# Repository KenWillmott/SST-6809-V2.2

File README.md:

# SST-6809-V2.2
This is the working repository for the most current and only recommended version of the SST-6809.
It contains all of the files and reference documents, and some documentation. However, the full documentation set will be hosted elsewhere, location is yet to be determined. For now, you can follow the documentation in the old repo "SST-6809" which is mostly concordant with this new version.

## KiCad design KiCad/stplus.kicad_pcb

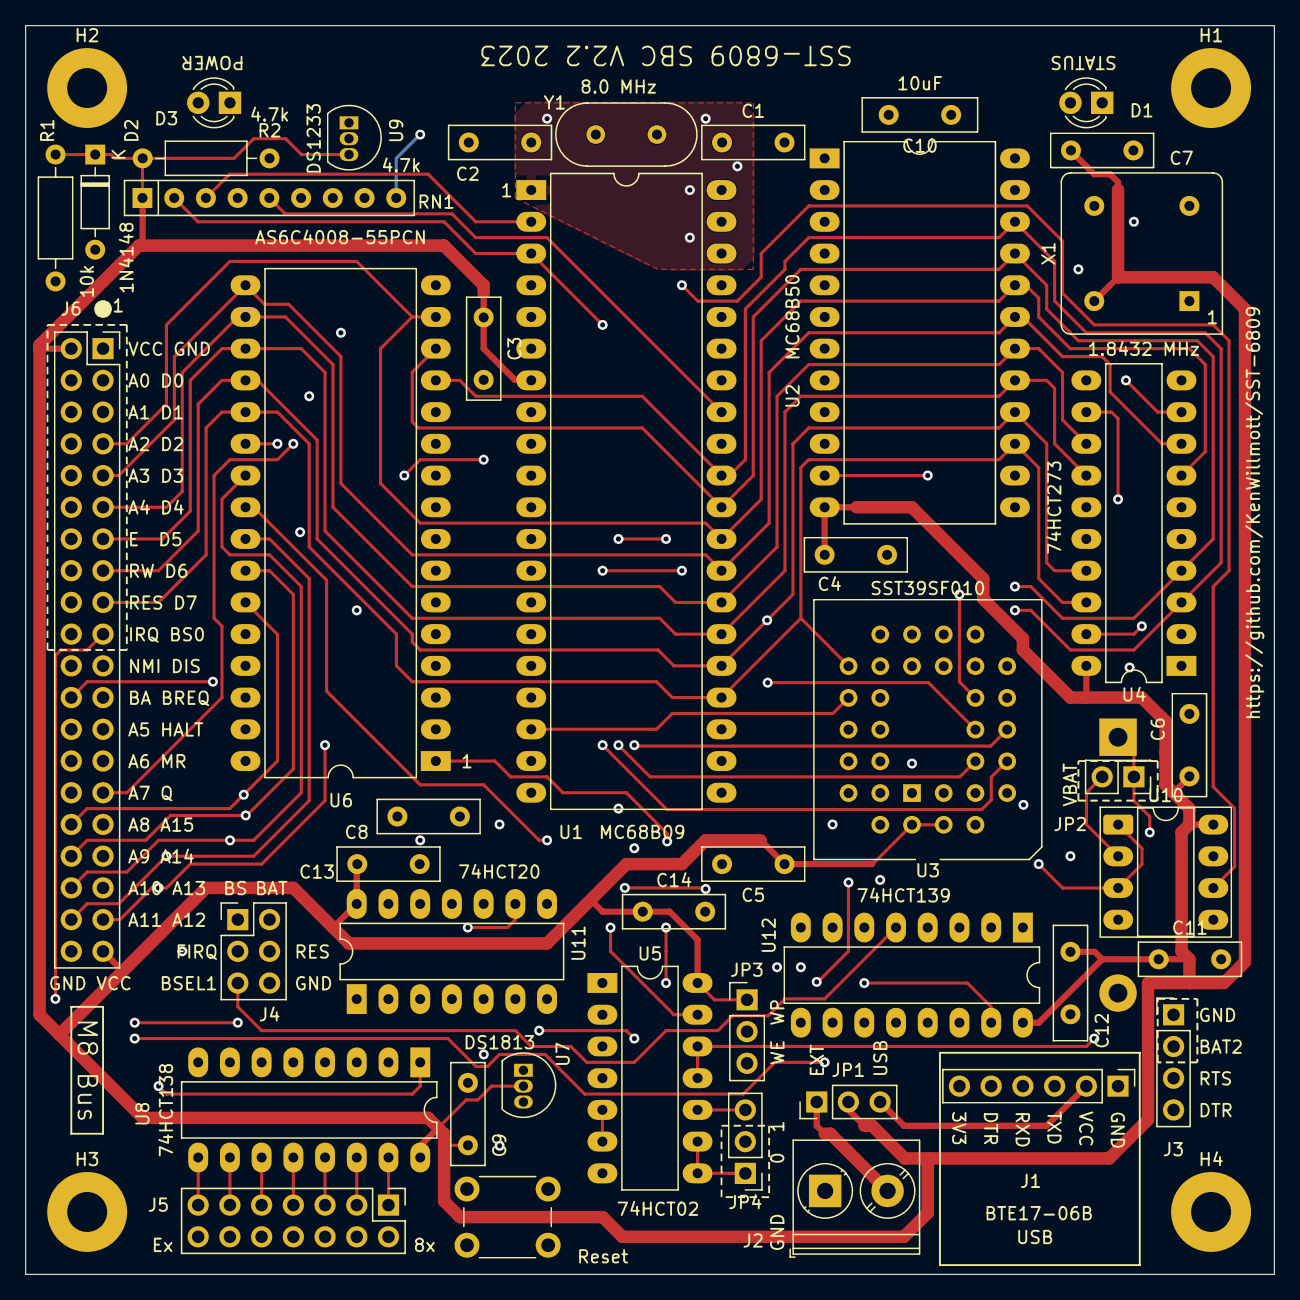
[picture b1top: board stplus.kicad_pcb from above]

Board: 4 copper layers, 100.0 x 100.0 mm, 50 parts (1 on the bottom side), 88 nets.

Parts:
BT1: 3.0V; BatteryHolder_Keystone_103_1x20mm
C1, C2: 20pF; C_Disc_D8.0mm_W2.5mm_P5.00mm
C3, C4, C5, C6, C7, C8, C9, C11, C13, C14: 100nF; C_Disc_D8.0mm_W2.5mm_P5.00mm
C10: 10uF; C_Disc_D9.0mm_W2.5mm_P5.00mm
C12: 100nF; C_Disc_D9.0mm_W2.5mm_P5.00mm
D1: STAT; LED_D3.0mm
D2: 1N4148; D_DO-35_SOD27_P7.62mm_Horizontal
D3: PWR; LED_D3.0mm
H1, H2, H3, H4: MountingHole_Pad; MountingHole_3.2mm_M3_Pad
J1: Conn_01x06_Pin; PinHeader_1x06_P2.54mm_Vertical
J2: Screw_Terminal_01x02; TerminalBlock_Phoenix_PT-1,5-2-5.0-H_1x02_P5.00mm_Horizontal
J3: Conn_01x04_Pin; PinHeader_1x04_P2.54mm_Vertical
J4: Conn_02x03_Odd_Even; PinHeader_2x03_P2.54mm_Vertical
J5: Conn_02x07_Odd_Even; PinHeader_2x07_P2.54mm_Vertical
J6: Conn_02x20_Odd_Even; PinSocket_2x20_P2.54mm_Vertical
JP1, JP3, JP4: Jumper_3_Bridged12; PinHeader_1x03_P2.54mm_Vertical
JP2: VBAT; PinHeader_2x01_P2.54mm_Vertical
R1: 10k; R_Axial_DIN0207_L6.3mm_D2.5mm_P10.16mm_Horizontal
R2: 4.7k; R_Axial_DIN0207_L6.3mm_D2.5mm_P10.16mm_Horizontal
RN1: 4.7k; R_Array_SIP9
SW1: Reset; SW_PUSH_6mm_H5mm
U1: MC68B09; DIP-40_W15.24mm_LongPads
U2: MC68B50; DIP-24_W15.24mm_LongPads
U3: SST39SF010; PLCC-32_THT-Socket
U4: 74HCT273; DIP-20_W7.62mm_LongPads
U5: 74HCT02; DIP-14_W7.62mm_LongPads
U6: AS6C4008-55PCN; DIP-32_W15.24mm_LongPads
U7: DS1813; TO-92L_Inline
U8: 74HCT138; DIP-16_W7.62mm_LongPads
U9: DS1233; TO-92L_Inline
U10: DS1210; DIP-8_W7.62mm_Socket_LongPads
U11: 74HCT20; DIP-14_W7.62mm_LongPads
U12: 74HCT139; DIP-16_W7.62mm_LongPads
X1: CXO_DIP8; Oscillator_DIP-8
Y1: 8.0 MHz; Crystal_HC18-U_Vertical

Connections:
/A0: J6.4, U1.8 (A0), U2.11 (RS), U3.12 (A0), U6.12 (A0)
/A1: J6.6, U1.9 (A1), U3.11 (A1), U6.11 (A1)
/A2: J6.8, U1.10 (A2), U3.10 (A2), U6.10 (A2)
/A3: J6.10, U1.11 (A3), U3.9 (A3), U6.9 (A3)
/A4: J6.12, U1.12 (A4), U3.8 (A4), U6.8 (A4)
/A5: J6.26, U1.13 (A5), U3.7 (A5), U6.7 (A5)
/A6: J6.28, U1.14 (A6), U3.6 (A6), U6.6 (A6)
/A7: J6.30, U1.15 (A7), U3.5 (A7), U6.5 (A7)
/A8: J6.32, U1.16 (A8), U2.10 (CS1), U3.27 (A8), U6.27 (A8), U11.10
/A9: J6.34, U1.17 (A9), U2.8 (CS0), U3.26 (A9), U6.26 (A9), U11.12
/A10: J6.36, U1.18 (A10), U3.23 (A10), U6.23 (A10), U12.2 (A0)
/A11: J6.38, U1.19 (A11), U3.25 (A11), U6.25 (A11), U12.3 (A1)
/A12: J6.37, U1.20 (A12), U6.4 (A12), U8.1 (A0)
/A13: J6.35, U1.21 (A13), U6.28 (A13), U8.2 (A1)
/A14: J6.33, U1.22 (A14), U6.3 (A14), U8.3 (A2)
/A15: J6.31, U1.23 (A15), U5.2, U8.6 (E2)
/A15G: U5.1, U6.31 (A15)
/D0: J6.3, U1.31 (D0), U2.22 (D0), U3.13 (D0), U4.3 (D0), U6.13 (DQ0)
/D1: J6.5, U1.30 (D1), U2.21 (D1), U3.14 (D1), U4.4 (D1), U6.14 (DQ1)
/D2: J6.7, U1.29 (D2), U2.20 (D2), U3.15 (D2), U4.7 (D2), U6.15 (DQ2)
/D3: J6.9, U1.28 (D3), U2.19 (D3), U3.17 (D3), U4.8 (D3), U6.17 (DQ3)
/D4: J6.11, U1.27 (D4), U2.18 (D4), U3.18 (D4), U4.13 (D4), U6.18 (DQ4)
/D5: J6.13, U1.26 (D5), U2.17 (D5), U3.19 (D5), U4.14 (D5), U6.19 (DQ5)
/D6: J6.15, U1.25 (D6), U2.16 (D6), U3.20 (D6), U4.17 (D6), U6.20 (DQ6)
/D7: J6.17, U1.24 (D7), U2.15 (D7), U3.21 (D7), U4.18 (D7), U6.21 (DQ7)
/DTR: J1.5, J3.4
/RTS: J3.3, U2.5 (~RTS)
/TXD: J1.4, U2.6 (Tx_Data)
/Z0: U4.2 (Q0), U5.3
/Z1: U4.5 (Q1), U6.2 (A16)
/Z2: U4.6 (Q2), U5.11, U5.12
/Z2*: U5.13, U6.30 (A17)
/Z3: U4.9 (Q3), U6.1 (A18)
/decode/ACIASEL*: U2.9 (CS2), U12.6 (O2)
/decode/BSEL1*: J4.5, U12.5 (O1)
/decode/EERD*: U3.24 (OE), U12.11 (O1)
/decode/EEWR*: JP3.2 (C), U3.31 (PGM)
/decode/LATSEL*: U4.11 (Cp), U11.8
/decode/NVBAT: BT1.1 (+), J4.2, JP2.1 (A)
/decode/NVCC: C8.1, U6.32 (VCC), U10.1 (VCCO), U10.3 (TOL)
/decode/NVCE*: U6.22 (CE#), U10.6 (~CEO)
/decode/NVRD*: U6.24 (OE#), U12.9 (O3)
/decode/NVWR*: U6.29 (WE#), U12.10 (O2)
/decode/Z6: JP4.1 (A), U4.16 (Q6), U5.8, U5.9
BA: J6.24, U1.6 (BA)
BREQ*: J6.23, RN1.5 (R4), U1.33 (~DMA/BREQ)
BS: J4.1, U1.5 (BS)
BSEL0*: J6.19, U12.4 (O0)
BT0: JP4.2 (C), U3.29 (A14)
DIS*: J6.21, RN1.4 (R3), U11.1
E: J6.14, U1.34 (E), U2.14 (E), U11.5, U11.9
FIRQ*: J4.3, RN1.8 (R7), U1.4 (~FIRQ)
GND: BT1.2 (-), C1.2, C2.2, C3.2, C4.2, C5.2, C6.2, C7.1, C8.2, C9.2, C10.2, C11.2, C12.2, C13.2, C14.2, D3.1 (K), H1.1, H2.1, H3.1, H4.1, J1.1, J2.1, J3.1, J4.6, J6.1, J6.40, SW1.2, U1.1 (VSS), U2.1 (VSS), U2.23 (~DCD), U2.24 (~CTS), U3.16 (GND), U3.22 (CE), U4.10 (GND), U5.7 (GND), U6.16 (VSS), U7.3 (GND), U8.4 (~E0), U8.5 (~E1), U8.8 (GND), U9.1 (GND), U10.4 (GND), U10.5 (~CE), U11.7 (GND), U12.8 (GND), X1.4 (GND)
HALT*: J6.25, RN1.6 (R5), U1.40 (~HALT)
IRQ*: J6.20, RN1.2 (R1), U1.3 (~IRQ), U2.7 (~IRQ)
MR: J6.27, RN1.7 (R6), U1.36 (MRDY)
NMI*: J6.22, RN1.3 (R2), U1.2 (~NMI)
unnamed: D1.2 (A), RN1.9 (R8)
unnamed: D3.2 (A), R2.2
unnamed: J1.2, JP1.3 (B)
unnamed: J2.2, JP1.1 (A)
unnamed: J5.1, U8.15 (~Y0)
unnamed: J5.3, U8.14 (~Y1)
unnamed: J5.5, U8.13 (~Y2)
unnamed: J5.7, U8.12 (~Y3)
unnamed: J5.9, U8.11 (~Y4)
unnamed: J5.2, J5.4, J5.6, J5.8, J5.10, J5.12, J5.14, U11.4, U12.1 (E)
unnamed: J5.11, U8.10 (~Y5)
unnamed: J5.13, U8.9 (~Y6)
unnamed: JP2.2 (B), U10.2 (VBAT1)
unnamed: JP3.3 (B), U12.12 (O0)
unnamed: JP4.3 (B), U5.10
unnamed: C2.1, U1.38 (EXTAL), Y1.2
unnamed: C1.1, U1.39 (XTAL), Y1.1
unnamed: U2.3 (Rx_CLK), U2.4 (Tx_CLK), X1.5 (OUT)
unnamed: U5.4, U11.13
unnamed: U5.5, U5.6, U12.7 (O3)
unnamed: U8.7 (~Y7), U12.13 (A1)
unnamed: U11.6, U12.15 (E)
Q: J6.29, U1.35 (Q)
RES*: C10.1, D2.2 (A), J4.4, J6.18, R1.2, SW1.1, U1.37 (~RESET), U4.1 (~Mr), U7.1 (~RESET), U9.2 (~RESET), U11.2
RXD: J1.3, U2.2 (Rx_Data)
R/W*: J6.16, U1.32 (R/~W), U2.13 (R/~W), U12.14 (A0)
VBAT2: J3.2, U10.7 (VBAT2)
VCC: C3.1, C4.1, C5.1, C6.1, C7.2, C9.1, C11.1, C12.1, C13.1, C14.1, D2.1 (K), J6.2, J6.39, JP1.2 (C), JP3.1 (A), R1.1, R2.1, RN1.1 (common), U1.7 (VCC), U2.12 (VCC), U3.2 (A16), U3.3 (A15), U3.32 (VCC), U4.20 (VCC), U5.14 (VCC), U7.2 (VCC), U8.16 (VCC), U9.3 (VCC), U10.8 (VCCI), U11.14 (VCC), U12.16 (VCC), X1.8 (Vcc)
Z4: U3.4 (A12), U4.12 (Q4)
Z5: U3.28 (A13), U4.15 (Q5)
Z7: D1.1 (K), U4.19 (Q7)

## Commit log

2026-05-10 Create LICENSE
2026-05-10 exported schematic
2026-05-10 Create foo
2026-05-10 add BOM
2026-05-11 add default flash image
2026-05-13 interactive BOM
